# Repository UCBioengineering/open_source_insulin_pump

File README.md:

# open_source_insulin_pump
This project was originally created by the team at UC Bioengineering, University of Canterbury, Christchurch, New Zealand.

This project has been modified and adapted by students at New Jersey Institute of Technology, Newark, New Jersey, United States.

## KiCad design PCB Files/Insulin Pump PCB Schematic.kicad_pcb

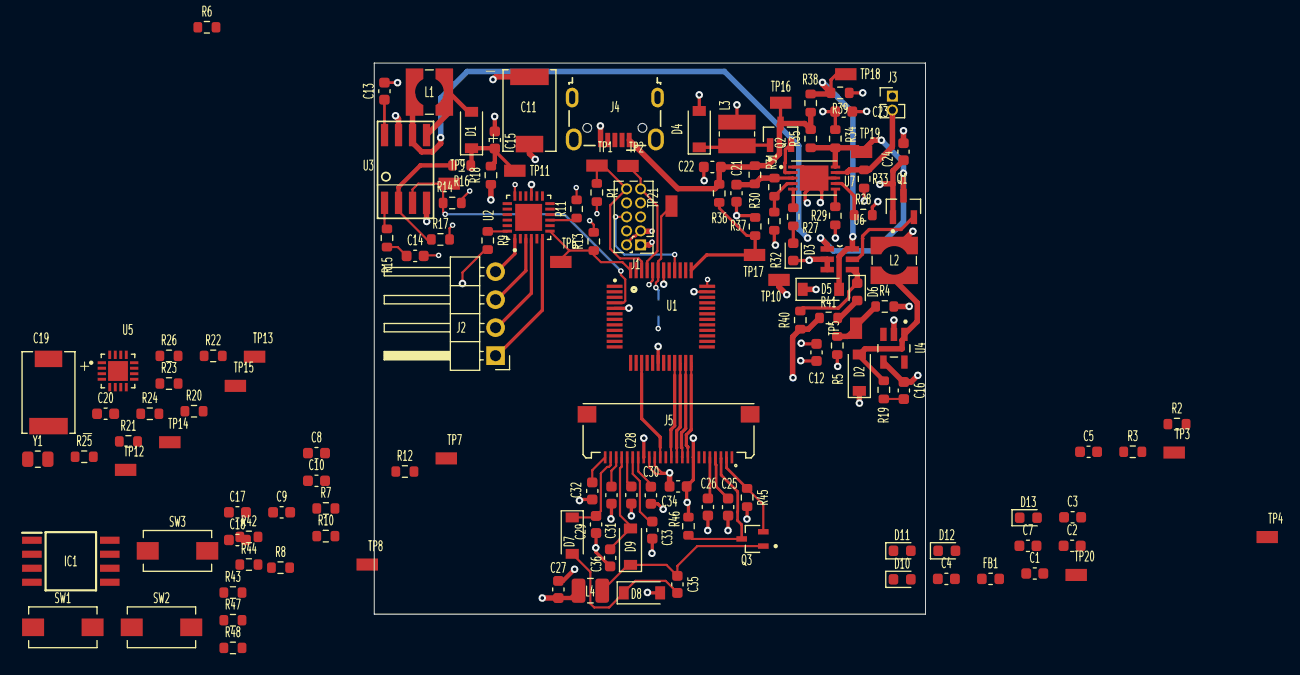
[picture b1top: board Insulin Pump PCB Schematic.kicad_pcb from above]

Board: 4 copper layers, 50.0 x 50.0 mm, 143 parts (1 on the bottom side), 93 nets.

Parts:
C1, C3, C8, C9, C12, C15, C22, C23, C24: 10uF; C_0603_1608Metric
C2, C4, C5, C10: 100nF; C_0603_1608Metric
C6, C21: 1uF; C_0603_1608Metric
C7: 100pF; C_0603_1608Metric
C11, C19: 70mF; CAP_DSK-3R3H703T414-HLL
C13: 33nF; C_0603_1608Metric
C14: 3.3nF; C_0603_1608Metric
C16: 120pF; C_0603_1608Metric
C17: 22uF; C_0603_1608Metric
C18: 47nF; C_0603_1608Metric
C20: 47pF; C_0603_1608Metric
C25, C26, C27, C28, C29, C30, C31, C32, C33, C36: 1uF/50V; C_0603_1608Metric
C34, C35: 4.7uF/50V; C_0603_1608Metric
D1, D2, D4, D5: D_Schottky; D_SOD-123
D3, D6, D10, D11, D12, D13: LED; D_0603_1608Metric
D7, D9: MBR0530; D_SOD-123
D8: MBRO530; D_SOD-123
FB1: Ferrite_Bead - 220 Ohm @ 100 MHz; L_0603_1608Metric
IC1: IS25LP128F-JBLE; SOIC127P790X216-8N
J1: Conn_02x05; PinHeader_2x05_P1.27mm_Vertical
J2: Conn_01x04_Male; PinHeader_1x04_P2.54mm_Horizontal
J3: Battery Connector; PinHeader_1x02_P1.27mm_Vertical
J4: USB_B_Micro; USB_Micro-B_Wuerth_629105150521
J5: XF2M-2415-1A; OMRON_XF2M-2415-1A
L1: Sumida CDRH4D28CNP-4R7PC 4.7uH; L_Wuerth_WE-TPC-3816
L2: 4.7uH; L_Wuerth_WE-TPC-3816
L3: SISCDRH74M-150R (Or equivalent) - 15uH; L_Wuerth_MAPI-3020
L4: Murata 1239AS-H-100M=P2 10uH 1A; L_1008_2520Metric
Q1, Q2: Q_PMOS_DGS G1S2G2D2S1D1; SOT95P230X110-3N
Q3: SI1308EDL; SOT65P210X110-3N
R1, R27, R34, R41: 1K; R_0603_1608Metric
R2: 330R; R_0603_1608Metric
R3: 2K2; R_0603_1608Metric
R4: 3K9; R_0603_1608Metric
R5, R6, R9, R10, R11, R12, R13, R17, R20, R21, R22, R23, R26, R31, R42, R43, R44, R45, R47, R48: 10K; R_0603_1608Metric
R7, R8: 500m; R_0603_1608Metric
R14, R37: 100K; R_0603_1608Metric
R15: 6K8; R_0603_1608Metric
R16: 30K; R_0603_1608Metric
R18, R25: 0R; R_0603_1608Metric
R19: 5R1; R_0603_1608Metric
R24: 1K5; R_0603_1608Metric
R28: 80K; R_0603_1608Metric
R29: 47K; R_0603_1608Metric
R30: 150R; R_0603_1608Metric
R32: 10K THERMISTOR; R_0603_1608Metric
R33: 0.1R; R_0603_1608Metric
R35: 270K; R_0603_1608Metric
R36: 51K; R_0603_1608Metric
R38: 10R; R_0603_1608Metric
R39: 15R; R_0603_1608Metric
R40: 470K; R_0603_1608Metric
R46: 0.47R; R_0603_1608Metric
SW1, SW2, SW3: SW_Push; SW_SPST_EVQPE1
TP1: SWDIO; TP+195X110
TP2: SWDCLK; TP+195X110
TP3: GND; TP+195X110
TP4: Reset; TP+195X110
TP5: ADC_BATT; TP+195X110
TP6: nFAULT; TP+195X110
TP7: STEP; TP+195X110
TP8: DIR; TP+195X110
TP9: BOOST_EN; TP+195X110
TP10: 3V; TP+195X110
TP11: BOOST_OUT; TP+195X110
TP12: MOSI; TP+195X110
TP13: SS_RTC; TP+195X110
TP14: SCLK; TP+195X110
TP15: MISO; TP+195X110
TP16: USB_5V; TP+195X110
TP17: USB_DETECT; TP+195X110
TP18: 3V0; TP+195X110
TP19: BATT+; TP+195X110
TP20: 3V3 MCU; TP+195X110
TP21: VDDCORE; TP+195X110
U1: ATSAMD21G18A-AUT; QFP50P900X900X120-48N
U2: DRV8846RGER; QFN50P400X400X100-25N
U3: ADP1612ARMZ-R7; SOIC-08
U4: TPS613221ADBVT; SOT95P280X145-5N
U5: AB1815; QFN50P300X300X90-17N
U6: LTC4412ES6TRMPBF; SOT95P280X100-6N
U7: DS2710G+; SON50P300X400X80-11N
Y1: SMD2012 (2.0mm *1.2mm) LFXTAL050789; R_0805_2012Metric

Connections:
+3V0: C12.1, C24.1, D5.1, L1.1, L2.1, Q1.1, R4.2, TP10.1, U3.6
+3V3: C3.1, C4.1, C5.1, C7.1, C16.1, C17.1, C18.1, C27.1, C34.2, D2.1, FB1.2, IC1.8, J1.1, J5.15, J5.16, L4.1, R1.2, R3.2, R6.2, R9.2, R13.2, R20.2, R21.2, R22.2, R23.2, R25.1, R26.1, R40.1, R41.1, R42.1, R43.1, R44.1, R47.2, R48.1, TP20.1, U1.17, U1.36, U1.44, U4.4
+5V: C9.2, C10.2, C11.1, R18.1, U2.15
+BATT: C23.1, J3.1, L3.2, R34.2
/ADC_BATT_TEST: R4.1, R5.2, TP5.1
/BOOST_EN: R14.1, TP9.1, U1.4, U3.3
/BUSY: J5.9, U1.24
/BUTTON_1: R42.2, SW1.1, U1.11
/BUTTON_2: R43.2, SW2.1, U1.10
/BUTTON_3: R44.2, SW3.1, U1.14
/Battery and Charge Management/VDD: C21.1, R30.1, R31.2, U7.3
/Battery and Charge Management/VN1: J3.2, R33.2, U7.9
/Battery and Charge Management/VP1: Q1.3, R34.1, R35.1, TP19.1, U6.1, U7.10
/DC: J5.11, U1.22
/DIR: TP8.1, U1.19, U2.13
/EINK_SS: J5.12, U1.21
/Eink/GDR: J5.2, Q3.2, R45.1
/Eink/PREVGH: C36.2, D9.2, J5.21
/Eink/PREVGL: C29.1, D7.1, J5.23
/Eink/RESE: J5.3, Q3.3, R46.1
/Eink/VCOM: C32.1, J5.24
/FLASH_SS: IC1.1, U1.2
/LED1: D10.2, U1.16
/LED2: D11.2, U1.26
/LED3: D12.2, U1.29
/LED4: D13.2, U1.32
/MISO: IC1.2, TP15.1, U1.13, U5.6
/MOSI: IC1.5, J5.14, TP12.1, U1.15, U5.9
/Motor Driver and Boost/ADEC: R6.1, U2.19, U2.23
/Motor Driver and Boost/AISEN: R7.2, U2.2
/Motor Driver and Boost/BISEN: R8.2, U2.5
/Motor Driver and Boost/FB: R16.2, R17.1, U3.2
/RES: J5.10, U1.23
/SCLK: IC1.6, J5.13, R26.2, TP14.1, U1.12, U5.7
/SS_RTC: TP13.1, U1.1, U5.12
/STEP: TP7.1, U1.20, U2.12
/SWDCLK: J1.9, TP2.1, U1.45
/SWDIO: J1.10, R1.1, TP1.1, U1.46
/USB_DETECT: R36.1, R37.2, TP17.1, U1.37
/VDDANA: C1.1, C2.1, FB1.1, U1.6
/VDDCORE: C6.1, TP21.1, U1.43
/nFAULT: R13.1, TP6.1, U1.48, U2.7
/nRST: C7.2, J1.6, R2.1, R3.1, U1.40, U5.11
GND: C1.2, C2.2, C3.2, C4.2, C5.2, C6.2, C8.2, C9.1, C10.1, C11.2, C12.2, C13.2, C14.2, C15.2, C17.2, C18.2, C19.2, C20.2, C21.2, C22.2, C23.2, C24.2, C25.2, C26.2, C27.2, C28.2, C29.2, C30.2, C31.2, C32.2, C33.2, C34.1, C36.1, D3.1, D4.2, D8.2, D10.1, D11.1, D12.1, D13.1, IC1.4, J1.2, J1.3, J4.5, J5.8, J5.17, R5.1, R7.1, R8.1, R10.2, R11.2, R12.2, R14.2, R17.2, R28.2, R29.1, R32.1, R33.1, R37.1, R39.1, R45.2, R46.2, SW1.2, SW2.2, SW3.2, TP3.1, U1.5, U1.18, U1.35, U1.42, U2.18, U3.4, U3.7, U4.2, U5.17, U6.2, U6.3, U7.1, U7.8, U7.11
unnamed: C8.1, U2.14, U2.17
unnamed: C13.1, U3.8
unnamed: C14.1, R15.2
unnamed: C15.1, D1.1, R16.1, R18.2, TP11.1
unnamed: C16.2, R19.1
unnamed: C19.1, R24.1
unnamed: C20.1, U5.14
unnamed: C25.1, J5.4
unnamed: C26.1, J5.5
unnamed: C28.1, J5.20
unnamed: C30.1, J5.18
unnamed: C31.1, J5.22
unnamed: C33.1, J5.19
unnamed: C35.1, D9.1, L4.2, Q3.1
unnamed: C35.2, D7.2, D8.1
unnamed: D1.2, L1.2, U3.5
unnamed: D2.2, L2.2, R19.2, U4.1
unnamed: D3.2, R27.1
unnamed: D4.1, L3.1, Q2.1
unnamed: D6.1, R40.2, U6.4
unnamed: D6.2, R41.2
unnamed: IC1.3, R47.1
unnamed: IC1.7, R48.2
unnamed: J2.1, U2.6
unnamed: J2.2, U2.4
unnamed: J2.3, U2.3
unnamed: J2.4, U2.1
unnamed: Q1.2, U6.5
unnamed: Q2.2, U7.2
unnamed: R2.2, TP4.1
unnamed: R9.1, U2.22, U2.24
unnamed: R10.1, U2.20, U2.21
unnamed: R11.1, U2.8, U2.9
unnamed: R12.1, U2.10, U2.11
unnamed: R15.1, U3.1
unnamed: R20.1, U5.3
unnamed: R21.1, U5.10
unnamed: R22.1, U5.2
unnamed: R23.1, U5.1
unnamed: R24.2, U5.5
unnamed: R25.2, U5.13
unnamed: R27.2, U7.5
unnamed: R28.1, U7.7
unnamed: R29.2, U7.6
unnamed: R31.1, R32.2, U7.4
unnamed: U5.15, Y1.2
unnamed: U5.16, Y1.1
VAA: C22.1, J4.1, Q2.3, R30.2, R35.2, R36.2, R38.2, TP16.1
VPP: D5.2, R38.1, R39.2, TP18.1, U6.6

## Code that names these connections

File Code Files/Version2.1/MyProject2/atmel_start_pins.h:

/*
 * Code generated from Atmel Start.
 *
 * This file will be overwritten when reconfiguring your Atmel Start project.
 * Please copy examples or other code you want to keep to a separate file
 * to avoid losing it when reconfiguring.
 */
#ifndef ATMEL_START_PINS_H_INCLUDED
#define ATMEL_START_PINS_H_INCLUDED

#include <hal_gpio.h>

// SAMD21 has 8 pin functions

#define GPIO_PIN_FUNCTION_A 0
#define GPIO_PIN_FUNCTION_B 1
#define GPIO_PIN_FUNCTION_C 2
#define GPIO_PIN_FUNCTION_D 3
#define GPIO_PIN_FUNCTION_E 4
#define GPIO_PIN_FUNCTION_F 5
#define GPIO_PIN_FUNCTION_G 6
#define GPIO_PIN_FUNCTION_H 7

#define SS_RTC GPIO(GPIO_PORTA, 0)
#define SS_FLASH GPIO(GPIO_PORTA, 1)
#define ADC_BATT_TEST GPIO(GPIO_PORTA, 2)
#define BOOST_EN GPIO(GPIO_PORTA, 3)
#define EINK_EN GPIO(GPIO_PORTA, 4)
#define BUTTON2 GPIO(GPIO_PORTA, 5)
#define BUTTON1 GPIO(GPIO_PORTA, 6)
#define SCK GPIO(GPIO_PORTA, 7)
#define MISO GPIO(GPIO_PORTA, 8)
#define BUTTON3 GPIO(GPIO_PORTA, 9)
#define MOSI GPIO(GPIO_PORTA, 10)
#define OUT1 GPIO(GPIO_PORTA, 11)
#define OUT2 GPIO(GPIO_PORTA, 12)
#define nFAULT GPIO(GPIO_PORTA, 13)
#define STEP GPIO(GPIO_PORTA, 14)
#define DIR GPIO(GPIO_PORTA, 15)
#define OUT3 GPIO(GPIO_PORTA, 16)
#define OUT4 GPIO(GPIO_PORTA, 17)
#define OUT5 GPIO(GPIO_PORTA, 18)
#define SCK_EXT GPIO(GPIO_PORTA, 19)
#define OUT6 GPIO(GPIO_PORTA, 20)
#define MISO_EXT GPIO(GPIO_PORTA, 22)
#define OUT7 GPIO(GPIO_PORTA, 23)
#define MOSI_EXT GPIO(GPIO_PORTA, 24)
#define APS_BUTTON1 GPIO(GPIO_PORTA, 25)
#define APS_BUTTON2 GPIO(GPIO_PORTA, 27)
#define APS_BUTTON3 GPIO(GPIO_PORTA, 28)
#define SWDCLK GPIO(GPIO_PORTA, 30)
#define SWDIO GPIO(GPIO_PORTA, 31)
#define BUSY GPIO(GPIO_PORTB, 2)
#define RES GPIO(GPIO_PORTB, 3)
#define DC_EINK GPIO(GPIO_PORTB, 8)
#define SS_EINK GPIO(GPIO_PORTB, 9)
#define OUT8 GPIO(GPIO_PORTB, 10)
#define OUT9 GPIO(GPIO_PORTB, 11)
#define USB_DETECT GPIO(GPIO_PORTB, 22)

#endif // ATMEL_START_PINS_H_INCLUDED

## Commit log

2021-03-11 added bom pdf document
2023-04-05 Creating test
2023-04-05 Committing Build of Original Project
2023-04-17 Register APSbuttons for Interrupt
    Added external interrupt handling in Buttons.c
2023-04-17 APS_BUTTON#
    Added APS_BUTTON# inturrupts
2023-04-17 Revert "APS_BUTTON#"
    This reverts commit 6ff3a7131b5b64fa21859a646df86c43c62df390.
2023-04-18 Building Insulin Pump
2023-04-18 Adding Boilerplate Arduino and Unit Test
    Added Boilerplate Arduino code to send signal to Insulin Pump.
    Added basic testing library for Arduino code.
